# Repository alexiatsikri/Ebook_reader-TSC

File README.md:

# Ebook_reader-TSC

## Pasi de implementare
1. Analiza documentatiei initiale
- Am urmarit schematicul si board layout-ul furnizate de profesor.
- Pe baza acestora, am reprodus designul electronic in Fusion Electronics, atat schematicul, cat si placa PCB.
2. Plasarea componentelor in PCB
- Am inceput sa asez componentele pe placa, respectand pozitionarea si orientarea optima pentru un traseu eficient si functional.
3. Rutarea traseelor
- Am efectuat manual rutarea traseelor de putere, pentru a ma asigura ca acestea sunt robuste si bine dimensionate.
- Pentru restul conexiunilor, am utilizat functia de autorouting pe ambele straturi: top si bottom.
- Am adaugat polygon pour pentru ambele straturi, pentru a realiza plane de masa.
4. Optimizarea layout-ului
- Am utilizat vias pentru a conecta planele de masa intre straturi si a completa zonele neconectate.
- Am aplicat via stitching pentru a imbunatati integritatea electrica.
5. Generarea modelului 3D al placii
- Am creat modelul 3D al placii pe baza designului 2D.
- Pentru aceasta, am cautat, descarcat si importat manual fiecare componenta 3D, apoi le-am pozitionat conform plasamentului din PCB-ul 2D.
- Pentru componenta test pad, nu am gasit un model 3D disponibil online, asa ca am fost nevoita sa il modelez manual, pentru a putea reprezenta corect placa in ansamblul 3D.
6. Integrarea in ansamblul final – Openbook Enclosure
- Am importat modelul 3D al placii in fisierul principal al carcasei: Openbook Enclosure.
- In acest fisier am plasat toate componentele in carcasa finala, astfel incat sa asigur o potrivire optima si functionala.
- Am desenat manual display-ul si bateria, pentru a le integra in ansamblu si a obtine o reprezentare cat mai realista a produsului final.

## Block Diagram

## Bill of Materials
| Componenta | Link | Datasheet |
|-----------|--------------|-----------|
| Buton | [Model](https://industry.panasonic.com/global/en/products/control/switch/light-touch/number/evqpuj02k) | [Datasheet](https://www.lcsc.com/datasheet/lcsc_datasheet_2201121800_PANASONIC-EVQPUJ02K_C2936858.pdf) |
| Capacitor | [Model](https://componentsearchengine.com/part-view/R0402%201%25%20100%20K%20(RC0402FR-07100KL)/YAGEO) | [Datasheet](//efaidnbmnnnibpcajpcglclefindmkaj/https://www.resistor.com/assets/pdf/0402tstd.pdf) |
| CPH3225A | [Model](https://www.snapeda.com/parts/CPH3225A/Seiko+Instruments/view-part/?ref=eda) | [Datasheet](https://octopart.com/datasheet/cph3225a-seiko-25340571) |
| EVQPUJ02K | [Model](https://industry.panasonic.com/global/en/products/control/switch/light-touch/number/evqpuj02k) | [Datasheet](https://www.lcsc.com/datasheet/lcsc_datasheet_2201121800_PANASONIC-EVQPUJ02K_C2936858.pdf) |
| KP-1608SURCK | [Model](https://www.snapeda.com/parts/KP-1608SURCK/Kingbright/view-part/?ref=search&t=LED%200603) | [Datasheet](//efaidnbmnnnibpcajpcglclefindmkaj/https://media.elv.com/file/107153_led_surck1608_data.pdf) |
| USBLC6-2SC6Y | [Model](https://www.snapeda.com/parts/USBLC6-2SC6Y/STMicroelectronics/view-part/?ref=eda) | [Datasheet](https://www.digikey.com/en/htmldatasheets/production/1375342/0/0/1/usblc6-2sc6y) |
| SD0805S020S1R0 | [Model](https://ro.mouser.com/ProductDetail/KYOCERA-AVX/SD0805S020S1R0?qs=jCA%252BPfw4LHbpkAoSnwrdjw%3D%3D) | [Datasheet](https://www.alldatasheet.com/view.jsp?Searchword=SD0805S&sField=2) |
| PGB1010603MR | [Model](https://www.snapeda.com/parts/PGB1010603MR/Littelfuse/view-part/?ref=eda) | [Datasheet](https://www.alldatasheet.com/view.jsp?Searchword=Pgb1010603mr&gad_source=1&gbraid=0AAAAADcdDU8aYfZtfJfdZ9I5j6RwZ_cbA&gclid=Cj0KCQjwqcO_BhDaARIsACz62vOPBOBe0eOh5gDUFkkKl4JBcbmoFZYtJ8BOnbaWqr_BuUCcVWvbutAaAmGkEALw_wcB) |
| BD5229G-TR  | [Model](https://componentsearchengine.com/part-view/BD5229G-TR/ROHM%20Semiconductor) | [Datasheet](https://www.lcsc.com/datasheet/lcsc_datasheet_2201131330_ROHM-Semicon-BD5229G-TR_C962636.pdf) |
| XC6220A331MR-G | [Model](https://componentsearchengine.com/part-view/XC6220A331MR-G/Torex) | [Datasheet](https://www.alldatasheet.com/view.jsp?Searchword=Xc6220&gad_source=1&gbraid=0AAAAADcdDU8aYfZtfJfdZ9I5j6RwZ_cbA&gclid=Cj0KCQjwqcO_BhDaARIsACz62vPS06NB6tLgniZzfaVpKNu1m811BNk6AEPfg4DbP6f5S8QWA_pW_UQaAv-0EALw_wcB) |
| XC6220A331MR-G | [Model](https://componentsearchengine.com/part-view/XC6220A331MR-G/Torex) | [Datasheet](https://www.alldatasheet.com/view.jsp?Searchword=Xc6220&gad_source=1&gbraid=0AAAAADcdDU8aYfZtfJfdZ9I5j6RwZ_cbA&gclid=Cj0KCQjwqcO_BhDaARIsACz62vMO5_aHsn35cIZBK6oCFuB_WOxz_zKu4yOHJ69-EnaUd5Jfas_Avm8aAuk5EALw_wcB) |
| USB4110-GF-A  | [Model](https://componentsearchengine.com/part-view/USB4110-GF-A/GCT%20(GLOBAL%20CONNECTOR%20TECHNOLOGY)) | [Datasheet](//efaidnbmnnnibpcajpcglclefindmkaj/https://gct.co/files/drawings/usb4110.pdf) |
| Adafruit | [Model](https://eu.mouser.com/ProductDetail/Adafruit/4208?qs=PzGy0jfpSMtbScLbr0L5dw%3D%3D) | [Datasheet](https://www.arrow.com/en/manufacturers/adafruit-industries/datasheets) |
| Bobina | [Model](https://store.comet.srl.ro/Catalogue/Product/43497/) | [Datasheet](https://www.scribd.com/document/814581278/Datasheet-Bobina) |
| PFMF | [Model](https://www.mouser.co.uk/ProductDetail/EPCOS-TDK/B72520T0350K062?qs=dEfas%2FXlABIszF52uu7vrg%3D%3D) | [Datasheet](https://ro.mouser.com/c/ds/circuit-protection/thermistors/resettable-fuses-pptc/?m=Schurter&series=PFMF) |
| DMG2305UX-7 | [Model](https://componentsearchengine.com/part-view/DMG2305UX-7/Diodes%20Incorporated) | [Datasheet](//efaidnbmnnnibpcajpcglclefindmkaj/https://www.mouser.com/datasheet/2/115/DMG2305UX-266242.pdf?srsltid=AfmBOop22k34YTJJra1xubiU6LPiN4M4JlcWbRoSNdxSGFak8uWgXPpK) |
| Si1308EDL-T1-GE3 | [Model](https://componentsearchengine.com/part-view/SI1308EDL-T1-GE3/Vishay) | [Datasheet](https://www.alldatasheet.com/view.jsp?Searchword=Si1308edl&gad_source=1&gbraid=0AAAAADcdDU-px713ONYSnQ2O-gcwqYcFq&gclid=Cj0KCQjwqcO_BhDaARIsACz62vN_Nz3MJOc6J_03gnVBm7aSqC8v9wyP0VD-iRKP-gFrYgdhLi99I14aAlVJEALw_wcB) |
| R0402 | [Model](https://componentsearchengine.com/part-view/R0402%201%25%20100%20K%20(RC0402FR-07100KL)/YAGEO) | [Datasheet](//efaidnbmnnnibpcajpcglclefindmkaj/https://www.resistor.com/assets/pdf/0402tstd.pdf) |
| BME680 | [Model](https://www.snapeda.com/parts/BME680/Bosch/view-part/?welcome=home) | [Datasheet](//efaidnbmnnnibpcajpcglclefindmkaj/https://www.bosch-sensortec.com/media/boschsensortec/downloads/datasheets/bst-bme680-ds001.pdf) |
| SMD Solder | [Model](https://grabcad.com/library/solder-jumpers-1) | [Datasheet]() |
| W25Q512JVEIQ | [Model](https://www.snapeda.com/parts/ESP32-C6-WROOM-1-N8/Espressif+Systems/view-part/?ref=eda) | [Datasheet](//efaidnbmnnnibpcajpcglclefindmkaj/https://www.mouser.com/datasheet/2/949/W25Q512JV_SPI_RevB_06252019_KMS-2487502.pdf?srsltid=AfmBOoquExqDVgxEELF9CzuOGxHos0CD1nQDROHD6Eebdm2foNzqozqU) |
| ESP32-C6-WROOM-1-N8 | [Model](https://www.snapeda.com/parts/ESP32-C6-WROOM-1-N8/Espressif+Systems/view-part/?ref=eda) | [Datasheet](//efaidnbmnnnibpcajpcglclefindmkaj/https://www.mouser.com/catalog/specsheets/Espressif_ESP32_C6_WROOM_1%20_Datasheet_V0.1_PRELIMINARY_en.pdf?srsltid=AfmBOooHQKNitqODRaaPjoZInfWKTacDER1t5uRK6sKqT13TrzvVo_B7) |
| DS3231SN# | [Model](https://www.snapeda.com/parts/DS3231SN%23/Analog+Devices/view-part/?ref=eda) | [Datasheet](https://www.alldatasheet.com/view.jsp?Searchword=Ds3231sn%20datasheet&gad_source=1&gbraid=0AAAAADcdDU-Gy9URfMxGmqiPg7ci5L3wR&gclid=Cj0KCQjwqcO_BhDaARIsACz62vMkK3ETSnW2w7mo0Fa-wgWJGn89AxWCyIND6k5X8MmoPl6hv6VWwT8aAiS-EALw_wcB) |
| MAX17048G+T10 | [Model](https://www.snapeda.com/parts/MAX17048G+T10/Analog+Devices/view-part/?ref=eda) | [Datasheet](https://www.alldatasheet.com/view.jsp?Searchword=Max17048&gad_source=1&gbraid=0AAAAADcdDU8aYfZtfJfdZ9I5j6RwZ_cbA&gclid=Cj0KCQjwqcO_BhDaARIsACz62vNa9xrVfzjCjADRwXD0RBbo4Nret3ywwteDGLJKZui8ZL8KdVlTE7caAvQxEALw_wcB) |
| MCP73831T-5ACI/OT | [Model](https://www.mouser.co.uk/ProductDetail/Microchip-Technology/MCP73831T-5ACI-OT?qs=hH%252BOa0VZEiAcgAcEkuamXg%3D%3D) | [Datasheet](//efaidnbmnnnibpcajpcglclefindmkaj/https://ww1.microchip.com/downloads/en/DeviceDoc/MCP73831-Family-Data-Sheet-DS20001984H.pdf) |

## Functionalitate Hardware

Proiectul are la baza un circuit electronic compact, conceput pentru un dispozitiv de tip E-Book. Componentele principale sunt:

###  USB-C + Protectie ESD
- Asigura alimentarea dispozitivului.
- Se conecteaza prin interfata USB.
- Include protectie ESD pentru siguranta suplimentara.

###  SD Card
- Serveste ca mediu de stocare pentru cartile electronice.
- Functioneaza la 3.3V si comunica prin SPI cu microcontrollerul.

###  E-Paper Display + Module Asociate
- Include E-Paper Drive Circuit, Display Header si modulul EPD Power.
- Display Header se conecteaza la microcontroller prin SPI.
- EPD Power genereaza tensiunile necesare, iar Drive Circuit furnizeaza semnalele de control.
- Consum maxim la refresh: 30mA (alb-negru) / 60mA (color); consum zero in inactivitate.

### Senzor de Mediu - BME688
- Masoara temperatura, umiditate, presiune si calitatea aerului.
- Comunica prin I2C si functioneaza la 3.3V.
- Consum: <1uA in standby, 1–2mA in functionare.

### Modul RTC - DS3231SN
- Pastreaza ora si data curenta chiar si cu microcontrollerul oprit.
- Functioneaza pe baterie, cristal integrat de 32KHz.
- Comunica prin I2C.
- Consum: 150uA normal, 1uA pe baterie.

###  Memorie Flash Externa - 64MB NOR
- Extinde spatiul de stocare al microcontrollerului.
- Interfata SPI.
- Consum redus: 30–50mA la scriere/stergere, 10–20uA in standby.

###  Regulator de Tensiune LDO
- Asigura 3.3V pentru microcontroller.
- Consum foarte mic (~8uA activ), ideal pentru dispozitive pe baterii.

###  Supraveghetor de Tensiune
- Monitorizeaza stabilitatea tensiunii.
- Previne pornirea in conditii de tensiune necorespunzatoare.

###  Conector Qwiic/Stemma QT
- Permite conectarea facila a senzorilor prin I2C.
- Suporta conectarea in lant fara cabluri suplimentare.

###  Controler Baterie Li-Po
- Gestioneaza incarcarea/descarcarea bateriei.
- Previne suprasarcina si descarcarea profunda.

## Microcontroller - ESP32-C5

Platforma principala este modulul **ESP32-C5-WROOM**, un microcontroller performant cu consum redus, conectivitate moderna si suport pentru multiple interfete:

- **Consum energetic estimat:**
  - Activ: 100–120mA
  - Idle: 10–15mA
  - Deep Sleep: 10–20uA
- **Conectivitate:** Wi-Fi 6 (2.4 GHz), Bluetooth 5, USB nativ
- **Interfete:** GPIO, SPI, I2C, UART

### Conexiuni ESP32-C6

| Functie                    | Pini ESP32-C6             |
|---------------------------|---------------------------|
| Alimentare & Reset        | 3V3, GND, EN              |
| USB-C                     | GPIO13 (USB_D+), GPIO14 (USB_D-) |
| SD Card (SPI)             | GPIO27 (MISO), GPIO7 (MOSI), GPIO6 (SCK), GPIO4 (SS_SD) |
| E-Paper Display           | GPIO11 (EPD_CS), GPIO5 (EPD_DC), GPIO21 (EPD_RST), GPIO26 (EPD_BUSY) |
| Senzor BME688 (I2C)       | GPIO19 (SDA), GPIO20 (SCL), GPIO17 (I2C_PW) |
| UART                      | TXD0, RXD0                |
| Flash Extern              | FLASH_CS                  |
| Alte functii              | IO/BOOT, RTC_PWM, RTC_RST, INT_RTC |

## Design PCB & Amplasare Componente

Amplasarea componentelor pe placa a fost realizata cu grija, respectand bune practici pentru performanta si fiabilitate:

- **ESP32-C6** – pozitionat sus, cu antena orientata spre exterior si zona PCB decupata pentru semnal clar.
- **USB-C** – centrat in partea de jos, aliniat cu carcasa.
- **Display Header** – lateral, cu decupaj dedicat pentru ribbon.
- **Qwiic Connector** – pe margine, spatiu suficient pentru conectare facila.
- **Baterie** – PCB decupat pentru a acomoda dimensiunea bateriei Li-Po.
  
 ## Erori

  La editarea PCB-ului am intampinat urmatoarele erori:
  
- Smd, Copper Width - Net Class: 1 POWER
- Smd-Hole, Board Outline Clearance
 Smd-Hole, Board Outline Clearance

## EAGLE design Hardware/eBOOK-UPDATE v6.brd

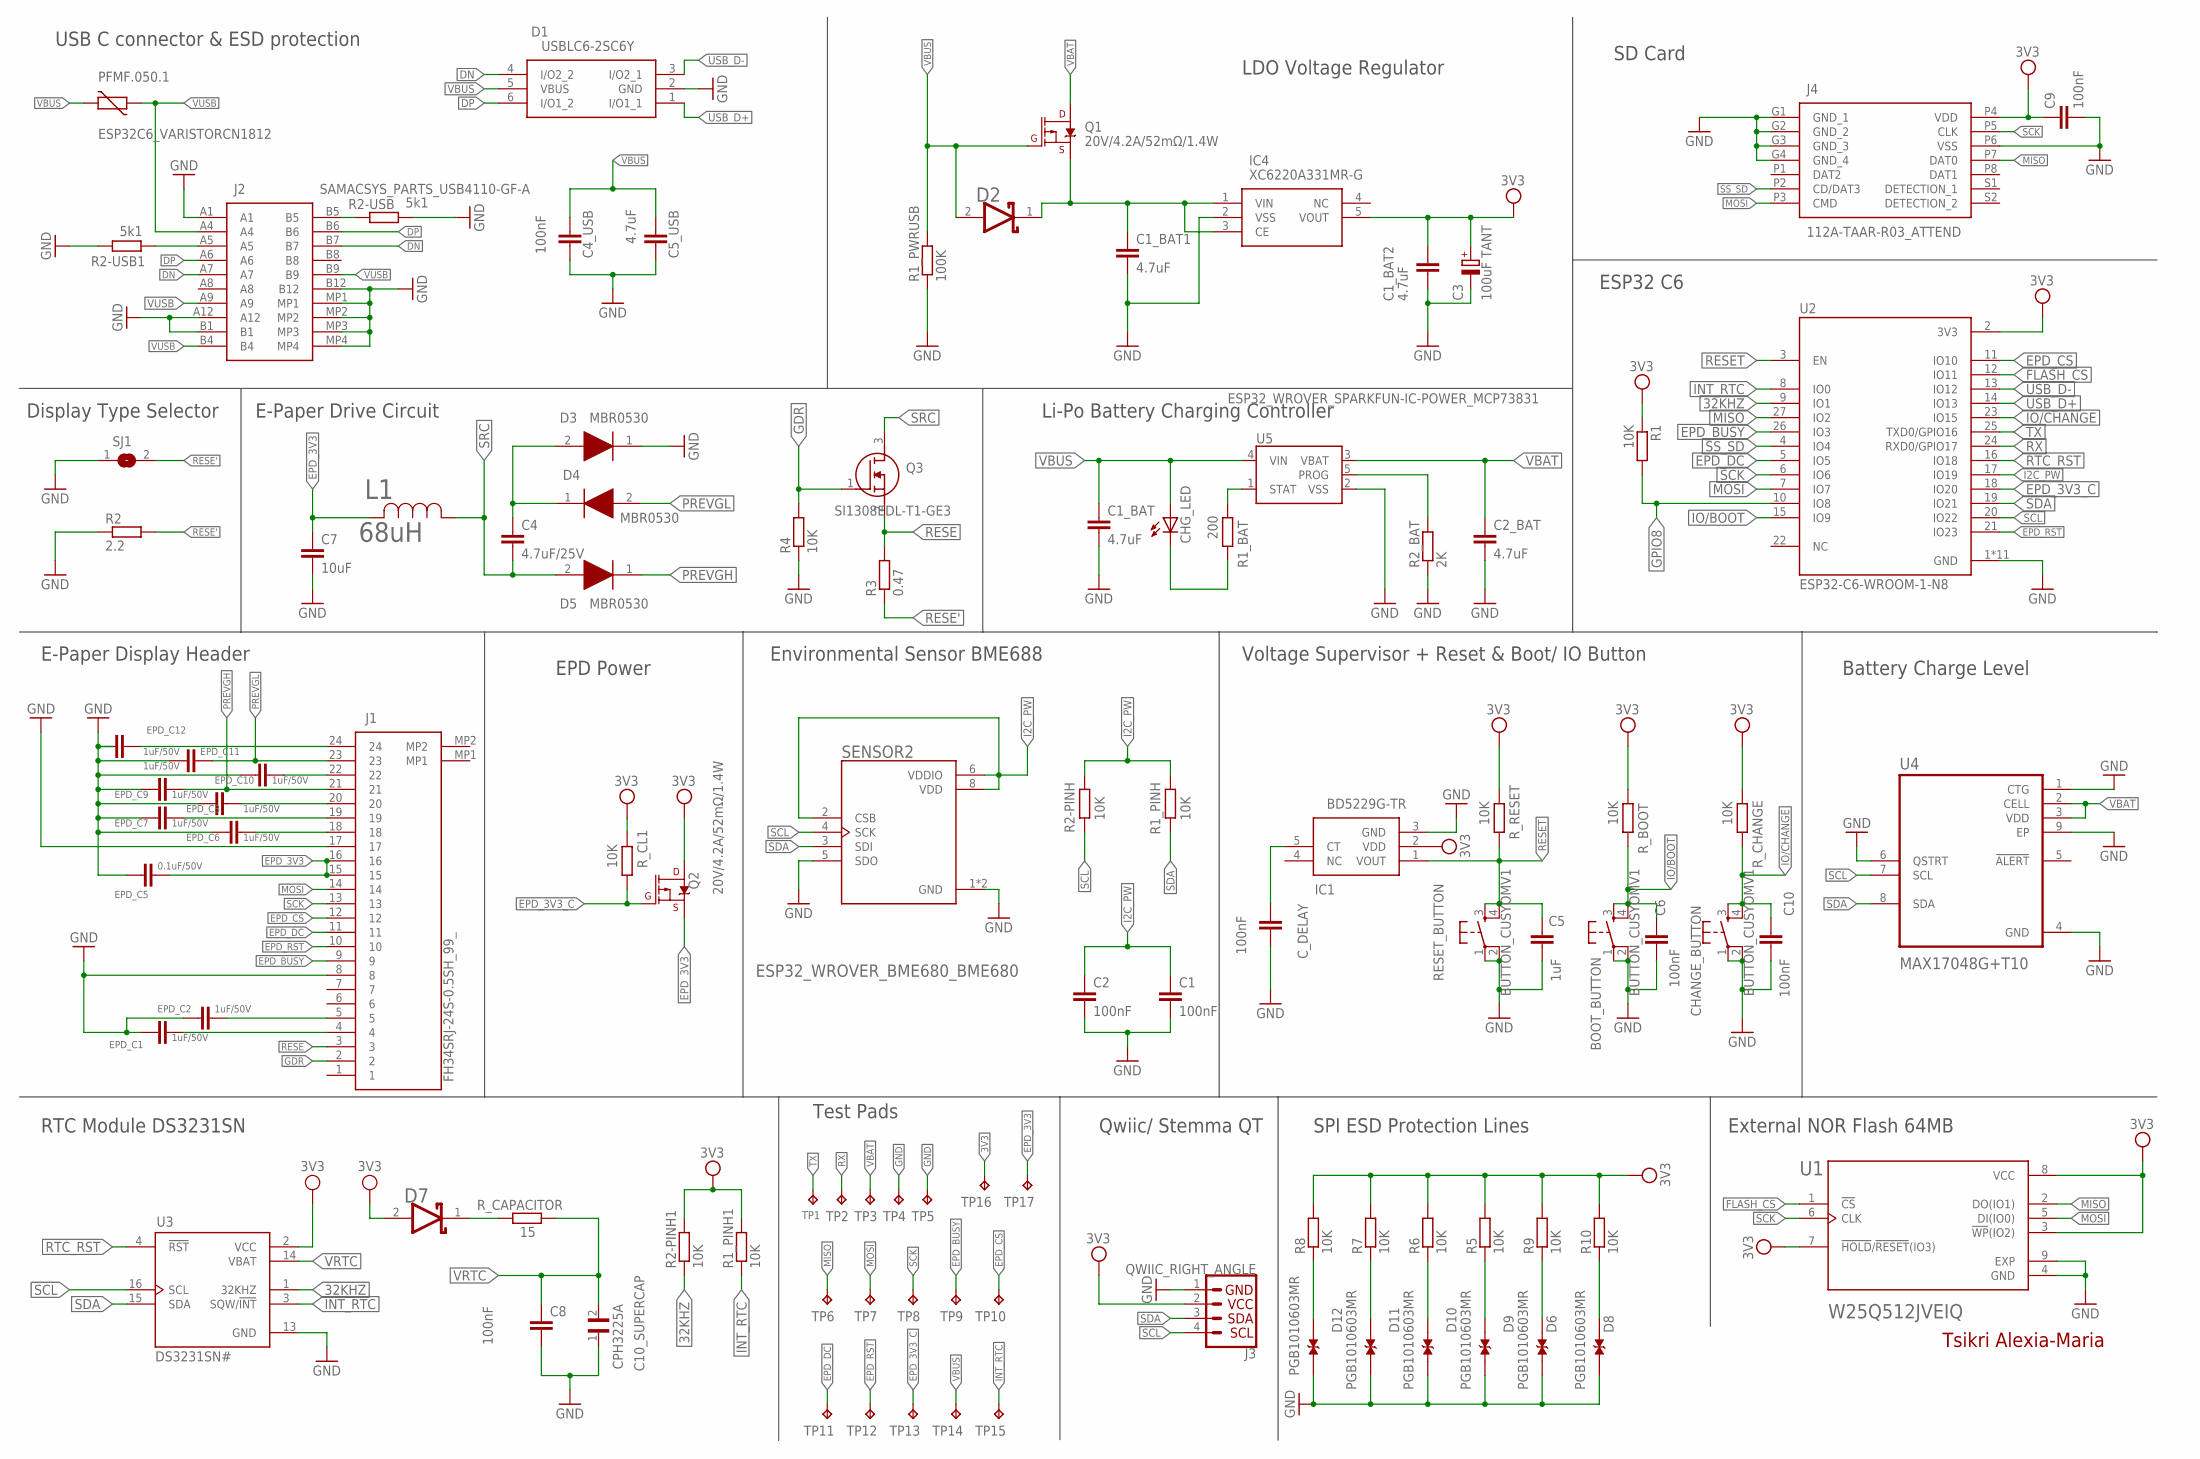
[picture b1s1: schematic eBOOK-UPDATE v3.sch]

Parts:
BOOT_BUTTON: BUTTON_CUSYOMV1; MYBUTTON
C1, C2, C4_USB, C6, C8, C9, C10: 100nF; ESP32_WROVER_EAGLE-LTSPICE_C0402
C1_BAT, C1_BAT1, C1_BAT2, C2_BAT, C5_USB: 4.7uF; ESP32_WROVER_EAGLE-LTSPICE_C0402
C3: 100uF TANT; RCL_CT3528
C4: 4.7uF/25V; ESP32_WROVER_EAGLE-LTSPICE_C0402
C5: 1uF; ESP32_WROVER_EAGLE-LTSPICE_C0402
C7: 10uF; ESP32_WROVER_EAGLE-LTSPICE_C0402
C10_SUPERCAP: CPH3225A; CAPCP3225X100N
CHANGE_BUTTON: BUTTON_CUSYOMV1; MYBUTTON
CHG_LED: ADAFRUIT_LEDCHIP-LED0603; ADAFRUIT_CHIP-LED0603
C_DELAY: 100nF; ESP32_WROVER_EAGLE-LTSPICE_C0402
D1: USBLC6-2SC6Y; SOT95P280X145-6N
D2, D7: ESP32_WROVER_AVX---SD0805S020S1R0_AVX_SD0805S020S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; ESP32_WROVER_AVX---SD0805S020S1R0_AVX_SD0805S020S1R0_0
D3, D4, D5: MBR0530; SOD3716X135N
D6, D8, D9, D10, D11, D12: PGB1010603MR; DIOC1608X36N
EPD_C1, EPD_C2, EPD_C6, EPD_C7, EPD_C8, EPD_C9, EPD_C10, EPD_C11, EPD_C12: 1uF/50V; ESP32_WROVER_EAGLE-LTSPICE_C0402
EPD_C5: 0.1uF/50V; ESP32_WROVER_EAGLE-LTSPICE_C0402
IC1: BD5229G-TR; SOT95P280X125-5N
IC4: XC6220A331MR-G; SOT95P280X120-5N
J1: FH34SRJ-24S-0.5SH_99_; FH34SRJ24S05SH99
J2: SAMACSYS_PARTS_USB4110-GF-A; SAMACSYS_PARTS_USB4110GFA
J3: QWIIC_RIGHT_ANGLE; JST04_1MM_RA
J4: 112A-TAAR-R03_ATTEND; 112ATAARR03ATTEND
L1: 68uH; IND_4828-WE-TPC_WRE
PFMF.050.1: ESP32C6_VARISTORCN1812; ESP32C6_VARISTOR_CT/CN1812
Q1, Q2: 20V/4.2A/52mΩ/1.4W; ESP32_WROVER_SPARKFUN-DISCRETESEMI_SOT23-3
Q3: SI1308EDL-T1-GE3; SOT65P210X110-3N
R1, R1_PINH, R1_PINH1, R2-PINH, R2-PINH1, R4, R5, R6, R7, R8, R9, R10: 10K; ESP32_WROVER_EAGLE-LTSPICE_R0402
R1_BAT: 200; ESP32_WROVER_EAGLE-LTSPICE_R0402
R1_PWRUSB: 100K; ESP32_WROVER_EAGLE-LTSPICE_R0402
R2: 2.2; ESP32_WROVER_EAGLE-LTSPICE_R0402
R2-USB, R2-USB1: 5k1; ESP32_WROVER_EAGLE-LTSPICE_R0402
R2_BAT: 2K; ESP32_WROVER_EAGLE-LTSPICE_R0402
R3: 0.47; ESP32_WROVER_EAGLE-LTSPICE_R0402
RESET_BUTTON: BUTTON_CUSYOMV1; MYBUTTON
R_BOOT: 10K; ESP32_WROVER_EAGLE-LTSPICE_R0402
R_CAPACITOR: 15; ESP32_WROVER_EAGLE-LTSPICE_R0402
R_CHANGE: 10K; ESP32_WROVER_EAGLE-LTSPICE_R0402
R_CL1: 10K; ESP32_WROVER_EAGLE-LTSPICE_R0402
R_RESET: 10K; ESP32_WROVER_EAGLE-LTSPICE_R0402
SENSOR2: ESP32_WROVER_BME680_BME680; ESP32_WROVER_BME680_PSON80P300X300X100-8N
SJ1: SJ
TP1, TP2, TP3, TP4, TP5, TP6, TP7, TP8, TP9, TP10, TP11, TP12, TP13, TP14, TP15, TP16, TP17: TPTP20R; TP20R
U1: W25Q512JVEIQ; SON127P600X800X80-9N
U2: ESP32-C6-WROOM-1-N8; XCVR_ESP32-C6-WROOM-1-N8
U3: DS3231SN#; SOIC127P1032X265-16N
U4: MAX17048G+T10; SON50P200X200X80-9N
U5: ESP32_WROVER_SPARKFUN-IC-POWER_MCP73831; ESP32_WROVER_SPARKFUN-IC-POWER_SOT23-5

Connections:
3V3: C1_BAT2.1, C3.+, C9.1, D7.2 (ANODE), IC1.2 (VDD), IC4.5 (VOUT), J3.2, J4.P4 (VDD), Q2.3 (D), R1.1, R1_PINH1.2, R2-PINH1.2, R5.2, R6.2, R7.2, R8.2, R9.2, R10.2, R_BOOT.2, R_CHANGE.2, R_CL1.2, R_RESET.2, TP16.TP, U1.3 (!WP!(IO2)), U1.7 (!HOLD!/!RESET!(IO3)), U1.8 (VCC), U2.2 (3V3), U3.2 (VCC)
32KHZ: R2-PINH1.1, U2.9 (IO1), U3.1 (32KHZ)
DN: D1.4 (I/O2_2), J2.A7, J2.B7
DP: D1.6 (I/O1_2), J2.A6, J2.B6
EPD_3V3: C7.1, EPD_C5.1, J1.15, J1.16, L1.2, Q2.2 (S), TP17.TP
EPD_3V3_C: Q2.1 (G), R_CL1.1, TP13.TP, U2.18 (IO20)
EPD_BUSY: J1.9, TP9.TP, U2.26 (IO3)
EPD_CS: J1.12, TP10.TP, U2.11 (IO10)
EPD_DC: J1.11, TP11.TP, U2.5 (IO5)
EPD_RST: J1.10, TP12.TP, U2.21 (IO23)
FLASH_CS: U1.1 (!CS), U2.12 (IO11)
GND: BOOT_BUTTON.1, BOOT_BUTTON.2, C1.2, C1_BAT.2, C1_BAT1.2, C1_BAT2.2, C2.2, C2_BAT.2, C3.-, C4_USB.2, C5.2, C5_USB.2, C6.2, C7.2, C8.2, C9.2, C10.2, C10_SUPERCAP.1, CHANGE_BUTTON.1, CHANGE_BUTTON.2, C_DELAY.2, D1.2 (GND), D3.1 (K), D6.1, D8.1, D9.1, D10.1, D11.1, D12.1, EPD_C1.2, EPD_C2.2, EPD_C5.2, EPD_C6.2, EPD_C7.2, EPD_C8.2, EPD_C9.2, EPD_C10.2, EPD_C11.2, EPD_C12.2, IC1.3 (GND), IC4.2 (VSS), J1.8, J1.17, J2.A1, J2.A12, J2.B1, J2.B12, J2.MP1, J2.MP2, J2.MP3, J2.MP4, J3.1, J4.G1 (GND_1), J4.G2 (GND_2), J4.G3 (GND_3), J4.G4 (GND_4), J4.P6 (VSS), R1_PWRUSB.1, R2.1, R2-USB.2, R2-USB1.1, R2_BAT.1, R4.1, RESET_BUTTON.1, RESET_BUTTON.2, SENSOR2.1 (GND), SENSOR2.5 (SDO), SENSOR2.7 (GND), SJ1.1, TP4.TP, TP5.TP, U1.4 (GND), U1.9 (EXP), U2.1 (GND), U2.28 (GND), U2.29_1 (GND), U2.29_2 (GND), U2.29_3 (GND), U2.29_4 (GND), U2.29_5 (GND), U2.29_6 (GND), U2.29_7 (GND), U2.29_8 (GND), U2.29_9 (GND), U3.13 (GND), U4.1 (CTG), U4.4 (GND), U4.6 (QSTRT), U4.9 (EP), U5.2 (VSS)
GPIO8: R1.2, U2.10 (IO8)
I2C_PW: C1.1, C2.1, R1_PINH.1, R2-PINH.1, SENSOR2.2 (CSB), SENSOR2.6 (VDDIO), SENSOR2.8 (VDD), U2.17 (IO19)
INT_RTC: R1_PINH1.1, TP15.TP, U2.8 (IO0), U3.3 (SQW/!INT)
IO/BOOT: BOOT_BUTTON.3, BOOT_BUTTON.4, C6.1, R_BOOT.1, U2.15 (IO9)
IO/CHANGE: C10.1, CHANGE_BUTTON.3, CHANGE_BUTTON.4, R_CHANGE.1, U2.23 (IO15)
MISO: J4.P7 (DAT0), TP6.TP, U1.2 (DO(IO1)), U2.27 (IO2)
MOSI: J1.14, J4.P3 (CMD), TP7.TP, U1.5 (DI(IO0)), U2.7 (IO7)
unnamed: D7.1 (CATHODE), R_CAPACITOR.1
unnamed: D8.2, R10.1
unnamed: D6.2, R9.1
unnamed: D9.2, R5.1
unnamed: D10.2, R6.1
unnamed: D11.2, R7.1
unnamed: D12.2, R8.1
unnamed: C_DELAY.1, IC1.5 (CT)
unnamed: J2.A5, R2-USB1.2
unnamed: C1_BAT1.1, D2.1 (CATHODE), IC4.1 (VIN), IC4.3 (CE), Q1.2 (S)
unnamed: R1_BAT.2, U5.1 (STAT)
unnamed: CHG_LED.C, R1_BAT.1
unnamed: J2.B5, R2-USB.1
unnamed: R2_BAT.2, U5.5 (PROG)
unnamed: EPD_C10.1, J1.22
unnamed: C4.1, D3.2 (A), D4.1 (K)
unnamed: EPD_C12.1, J1.24
unnamed: EPD_C8.1, J1.20
unnamed: EPD_C7.1, J1.19
unnamed: EPD_C6.1, J1.18
unnamed: EPD_C2.1, J1.5
unnamed: EPD_C1.1, J1.4
PREVGH: D5.1 (K), EPD_C9.1, J1.21
PREVGL: D4.2 (A), EPD_C11.1, J1.23
RESE: J1.3, Q3.2 (S), R3.2
RESE': R2.2, R3.1, SJ1.2
RESET: C5.1, IC1.1 (VOUT), RESET_BUTTON.3, RESET_BUTTON.4, R_RESET.1, U2.3 (EN)
RTC_RST: U2.16 (IO18), U3.4 (!RST)
RX: TP2.TP, U2.24 (RXD0/GPIO17)
SCK: J1.13, J4.P5 (CLK), TP8.TP, U1.6 (CLK), U2.6 (IO6)
SCL: J3.4, R2-PINH.2, SENSOR2.4 (SCK), U2.20 (IO22), U3.16 (SCL), U4.7 (SCL)
SDA: J3.3, R1_PINH.2, SENSOR2.3 (SDI), U2.19 (IO21), U3.15 (SDA), U4.8 (SDA)
SRC: C4.2, D5.2 (A), L1.1, Q3.3 (D)
SS_SD: J4.P2 (CD/DAT3), U2.4 (IO4)
TX: TP1.TP, U2.25 (TXD0/GPIO16)
USB_D+: D1.1 (I/O1_1), U2.14 (IO13)
USB_D-: D1.3 (I/O2_1), U2.13 (IO12)
VBAT: C2_BAT.1, Q1.3 (D), TP3.TP, U4.2 (CELL), U4.3 (VDD), U5.3 (VBAT)
VBUS: C1_BAT.1, C4_USB.1, C5_USB.1, CHG_LED.A, D1.5 (VBUS), D2.2 (ANODE), PFMF.050.1.2, Q1.1 (G), R1_PWRUSB.2, TP14.TP, U5.4 (VIN)
VRTC: C8.1, C10_SUPERCAP.2, R_CAPACITOR.2, U3.14 (VBAT)
VUSB: J2.A4, J2.A9, J2.B4, J2.B9, PFMF.050.1.1

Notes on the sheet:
External NOR Flash 64MB
SPI ESD Protection Lines
Qwiic/ Stemma QT
Test Pads
RTC Module DS3231SN
USB C connector & ESD protection
LDO Voltage Regulator
SD Card
ESP32 C6
Li-Po Battery Charging Controller
E-Paper Drive Circuit
Display Type Selector
E-Paper Display Header
EPD Power
Environmental Sensor BME688
Voltage Supervisor + Reset & Boot/ IO Button
Battery Charge Level
Tsikri Alexia-Maria

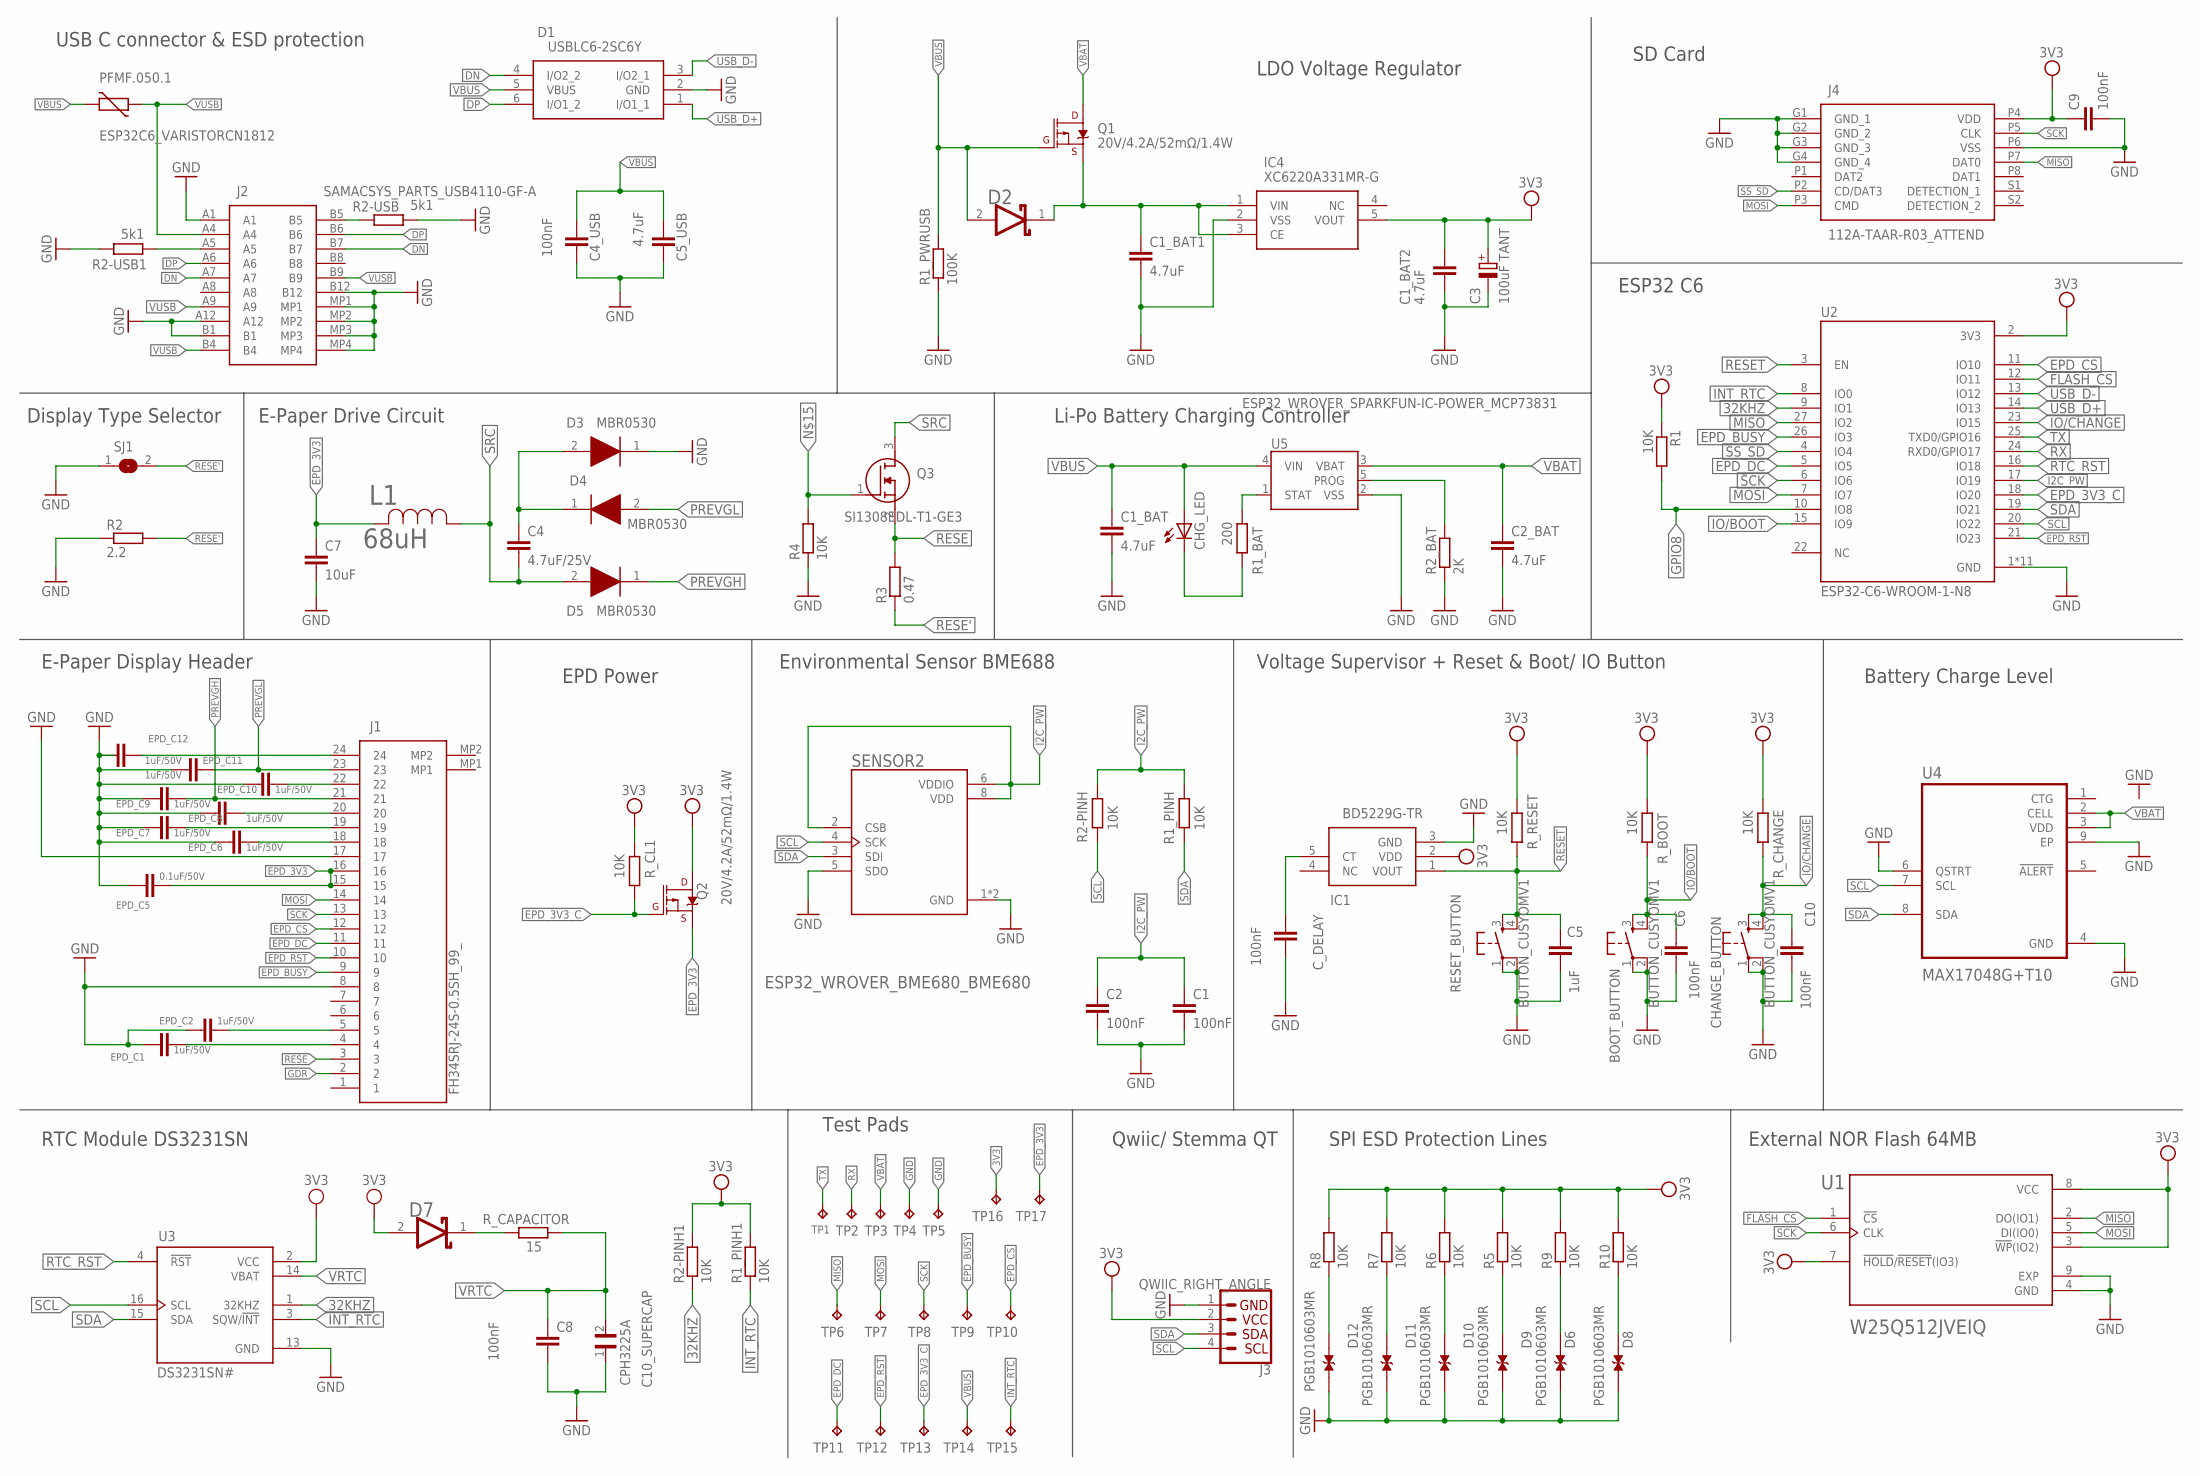
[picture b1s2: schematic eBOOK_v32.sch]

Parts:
BOOT_BUTTON: BUTTON_CUSYOMV1; MYBUTTON
C1, C2, C4_USB, C6, C8, C9, C10: 100nF; ESP32_WROVER_EAGLE-LTSPICE_C0402
C1_BAT, C1_BAT1, C1_BAT2, C2_BAT, C5_USB: 4.7uF; ESP32_WROVER_EAGLE-LTSPICE_C0402
C3: 100uF TANT; RCL_CT3528
C4: 4.7uF/25V; ESP32_WROVER_EAGLE-LTSPICE_C0402
C5: 1uF; ESP32_WROVER_EAGLE-LTSPICE_C0402
C7: 10uF; ESP32_WROVER_EAGLE-LTSPICE_C0402
C10_SUPERCAP: CPH3225A; CAPCP3225X100N
CHANGE_BUTTON: BUTTON_CUSYOMV1; MYBUTTON
CHG_LED: ADAFRUIT_LEDCHIP-LED0603; ADAFRUIT_CHIP-LED0603
C_DELAY: 100nF; ESP32_WROVER_EAGLE-LTSPICE_C0402
D1: USBLC6-2SC6Y; SOT95P280X145-6N
D2, D7: ESP32_WROVER_AVX---SD0805S020S1R0_AVX_SD0805S020S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; ESP32_WROVER_AVX---SD0805S020S1R0_AVX_SD0805S020S1R0_0
D3, D4, D5: MBR0530; SOD3716X135N
D6, D8, D9, D10, D11, D12: PGB1010603MR; DIOC1608X36N
EPD_C1, EPD_C2, EPD_C6, EPD_C7, EPD_C8, EPD_C9, EPD_C10, EPD_C11, EPD_C12: 1uF/50V; ESP32_WROVER_EAGLE-LTSPICE_C0402
EPD_C5: 0.1uF/50V; ESP32_WROVER_EAGLE-LTSPICE_C0402
IC1: BD5229G-TR; SOT95P280X125-5N
IC4: XC6220A331MR-G; SOT95P280X120-5N
J1: FH34SRJ-24S-0.5SH_99_; FH34SRJ24S05SH99
J2: SAMACSYS_PARTS_USB4110-GF-A; SAMACSYS_PARTS_USB4110GFA
J3: QWIIC_RIGHT_ANGLE; JST04_1MM_RA
J4: 112A-TAAR-R03_ATTEND; 112ATAARR03ATTEND
L1: 68uH; IND_4828-WE-TPC_WRE
PFMF.050.1: ESP32C6_VARISTORCN1812; ESP32C6_VARISTOR_CT/CN1812
Q1, Q2: 20V/4.2A/52mΩ/1.4W; ESP32_WROVER_SPARKFUN-DISCRETESEMI_SOT23-3
Q3: SI1308EDL-T1-GE3; SOT65P210X110-3N
R1, R1_PINH, R1_PINH1, R2-PINH, R2-PINH1, R4, R5, R6, R7, R8, R9, R10: 10K; ESP32_WROVER_EAGLE-LTSPICE_R0402
R1_BAT: 200; ESP32_WROVER_EAGLE-LTSPICE_R0402
R1_PWRUSB: 100K; ESP32_WROVER_EAGLE-LTSPICE_R0402
R2: 2.2; ESP32_WROVER_EAGLE-LTSPICE_R0402
R2-USB, R2-USB1: 5k1; ESP32_WROVER_EAGLE-LTSPICE_R0402
R2_BAT: 2K; ESP32_WROVER_EAGLE-LTSPICE_R0402
R3: 0.47; ESP32_WROVER_EAGLE-LTSPICE_R0402
RESET_BUTTON: BUTTON_CUSYOMV1; MYBUTTON
R_BOOT: 10K; ESP32_WROVER_EAGLE-LTSPICE_R0402
R_CAPACITOR: 15; ESP32_WROVER_EAGLE-LTSPICE_R0402
R_CHANGE: 10K; ESP32_WROVER_EAGLE-LTSPICE_R0402
R_CL1: 10K; ESP32_WROVER_EAGLE-LTSPICE_R0402
R_RESET: 10K; ESP32_WROVER_EAGLE-LTSPICE_R0402
SENSOR2: ESP32_WROVER_BME680_BME680; ESP32_WROVER_BME680_PSON80P300X300X100-8N
SJ1: SJ
TP1, TP2, TP3, TP4, TP5, TP6, TP7, TP8, TP9, TP10, TP11, TP12, TP13, TP14, TP15, TP16, TP17: TPTP20R; TP20R
U1: W25Q512JVEIQ; SON127P600X800X80-9N
U2: ESP32-C6-WROOM-1-N8; XCVR_ESP32-C6-WROOM-1-N8
U3: DS3231SN#; SOIC127P1032X265-16N
U4: MAX17048G+T10; SON50P200X200X80-9N
U5: ESP32_WROVER_SPARKFUN-IC-POWER_MCP73831; ESP32_WROVER_SPARKFUN-IC-POWER_SOT23-5

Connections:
3V3: C1_BAT2.1, C3.+, C9.1, D7.2 (ANODE), IC1.2 (VDD), IC4.5 (VOUT), J3.2, J4.P4 (VDD), Q2.3 (D), R1.1, R1_PINH1.2, R2-PINH1.2, R5.2, R6.2, R7.2, R8.2, R9.2, R10.2, R_BOOT.2, R_CHANGE.2, R_CL1.2, R_RESET.2, TP16.TP, U1.3 (!WP!(IO2)), U1.7 (!HOLD!/!RESET!(IO3)), U1.8 (VCC), U2.2 (3V3), U3.2 (VCC)
32KHZ: R2-PINH1.1, U2.9 (IO1), U3.1 (32KHZ)
DN: D1.4 (I/O2_2), J2.A7, J2.B7
DP: D1.6 (I/O1_2), J2.A6, J2.B6
EPD_3V3: C7.1, EPD_C5.1, J1.15, J1.16, L1.2, Q2.2 (S), TP17.TP
EPD_3V3_C: Q2.1 (G), R_CL1.1, TP13.TP, U2.18 (IO20)
EPD_BUSY: J1.9, TP9.TP, U2.26 (IO3)
EPD_CS: J1.12, TP10.TP, U2.11 (IO10)
EPD_DC: J1.11, TP11.TP, U2.5 (IO5)
EPD_RST: J1.10, TP12.TP, U2.21 (IO23)
FLASH_CS: U1.1 (!CS), U2.12 (IO11)
GND: BOOT_BUTTON.1, BOOT_BUTTON.2, C1.2, C1_BAT.2, C1_BAT1.2, C1_BAT2.2, C2.2, C2_BAT.2, C3.-, C4_USB.2, C5.2, C5_USB.2, C6.2, C7.2, C8.2, C9.2, C10.2, C10_SUPERCAP.1, CHANGE_BUTTON.1, CHANGE_BUTTON.2, C_DELAY.2, D1.2 (GND), D3.1 (K), D6.1, D8.1, D9.1, D10.1, D11.1, D12.1, EPD_C1.2, EPD_C2.2, EPD_C5.2, EPD_C6.2, EPD_C7.2, EPD_C8.2, EPD_C9.2, EPD_C10.2, EPD_C11.2, EPD_C12.2, IC1.3 (GND), IC4.2 (VSS), J1.8, J1.17, J2.A1, J2.A12, J2.B1, J2.B12, J2.MP1, J2.MP2, J2.MP3, J2.MP4, J3.1, J4.G1 (GND_1), J4.G2 (GND_2), J4.G3 (GND_3), J4.G4 (GND_4), J4.P6 (VSS), R1_PWRUSB.1, R2.1, R2-USB.2, R2-USB1.1, R2_BAT.1, R4.1, RESET_BUTTON.1, RESET_BUTTON.2, SENSOR2.1 (GND), SENSOR2.5 (SDO), SENSOR2.7 (GND), SJ1.1, TP4.TP, TP5.TP, U1.4 (GND), U1.9 (EXP), U2.1 (GND), U2.28 (GND), U2.29_1 (GND), U2.29_2 (GND), U2.29_3 (GND), U2.29_4 (GND), U2.29_5 (GND), U2.29_6 (GND), U2.29_7 (GND), U2.29_8 (GND), U2.29_9 (GND), U3.13 (GND), U4.4 (GND), U4.6 (QSTRT), U4.9 (EP), U5.2 (VSS); also elsewhere on the board
GPIO8: R1.2, U2.10 (IO8)
I2C_PW: C1.1, C2.1, R1_PINH.1, R2-PINH.1, SENSOR2.2 (CSB), SENSOR2.6 (VDDIO), SENSOR2.8 (VDD), U2.17 (IO19)
INT_RTC: R1_PINH1.1, TP15.TP, U2.8 (IO0), U3.3 (SQW/!INT)
IO/BOOT: BOOT_BUTTON.3, BOOT_BUTTON.4, C6.1, R_BOOT.1, U2.15 (IO9)
IO/CHANGE: C10.1, CHANGE_BUTTON.3, CHANGE_BUTTON.4, R_CHANGE.1, U2.23 (IO15)
MISO: J4.P7 (DAT0), TP6.TP, U1.2 (DO(IO1)), U2.27 (IO2)
MOSI: J1.14, J4.P3 (CMD), TP7.TP, U1.5 (DI(IO0)), U2.7 (IO7)
unnamed: D7.1 (CATHODE), R_CAPACITOR.1
unnamed: D8.2, R10.1
unnamed: D6.2, R9.1
unnamed: D9.2, R5.1
unnamed: D10.2, R6.1
unnamed: D11.2, R7.1
unnamed: D12.2, R8.1
unnamed: C_DELAY.1, IC1.5 (CT)
unnamed: J2.A5, R2-USB1.2
unnamed: C1_BAT1.1, D2.1 (CATHODE), IC4.1 (VIN), IC4.3 (CE), Q1.2 (S)
unnamed: R1_BAT.2, U5.1 (STAT)
unnamed: CHG_LED.C, R1_BAT.1
unnamed: J2.B5, R2-USB.1
unnamed: R2_BAT.2, U5.5 (PROG)
unnamed: EPD_C10.1, J1.22
unnamed: C4.1, D3.2 (A), D4.1 (K)
unnamed: EPD_C12.1, J1.24
unnamed: EPD_C8.1, J1.20
unnamed: EPD_C7.1, J1.19
unnamed: EPD_C6.1, J1.18
unnamed: EPD_C2.1, J1.5
unnamed: EPD_C1.1, J1.4
PREVGH: D5.1 (K), EPD_C9.1, J1.21
PREVGL: D4.2 (A), EPD_C11.1, J1.23
RESE: J1.3, Q3.2 (S), R3.2
RESE': R2.2, R3.1, SJ1.2
RESET: C5.1, IC1.1 (VOUT), RESET_BUTTON.3, RESET_BUTTON.4, R_RESET.1, U2.3 (EN)
RTC_RST: U2.16 (IO18), U3.4 (!RST)
RX: TP2.TP, U2.24 (RXD0/GPIO17)
SCK: J1.13, J4.P5 (CLK), TP8.TP, U1.6 (CLK), U2.6 (IO6)
SCL: J3.4, R2-PINH.2, SENSOR2.4 (SCK), U2.20 (IO22), U3.16 (SCL), U4.7 (SCL)
SDA: J3.3, R1_PINH.2, SENSOR2.3 (SDI), U2.19 (IO21), U3.15 (SDA), U4.8 (SDA)
SRC: C4.2, D5.2 (A), L1.1, Q3.3 (D)
SS_SD: J4.P2 (CD/DAT3), U2.4 (IO4)
TX: TP1.TP, U2.25 (TXD0/GPIO16)
USB_D+: D1.1 (I/O1_1), U2.14 (IO13)
USB_D-: D1.3 (I/O2_1), U2.13 (IO12)
VBAT: C2_BAT.1, Q1.3 (D), TP3.TP, U4.2 (CELL), U4.3 (VDD), U5.3 (VBAT)
VBUS: C1_BAT.1, C4_USB.1, C5_USB.1, CHG_LED.A, D1.5 (VBUS), D2.2 (ANODE), PFMF.050.1.2, Q1.1 (G), R1_PWRUSB.2, TP14.TP, U5.4 (VIN)
VRTC: C8.1, C10_SUPERCAP.2, R_CAPACITOR.2, U3.14 (VBAT)
VUSB: J2.A4, J2.A9, J2.B4, J2.B9, PFMF.050.1.1

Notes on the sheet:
External NOR Flash 64MB
SPI ESD Protection Lines
Qwiic/ Stemma QT
Test Pads
RTC Module DS3231SN
USB C connector & ESD protection
LDO Voltage Regulator
SD Card
ESP32 C6
Li-Po Battery Charging Controller
E-Paper Drive Circuit
Display Type Selector
E-Paper Display Header
EPD Power
Environmental Sensor BME688
Voltage Supervisor + Reset & Boot/ IO Button
Battery Charge Level

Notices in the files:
parts and their libraries:
DeskAssistant v19 v1: COPYRIGHT: Copyright (C) 2024 Ultra Librarian. All rights reserved.
